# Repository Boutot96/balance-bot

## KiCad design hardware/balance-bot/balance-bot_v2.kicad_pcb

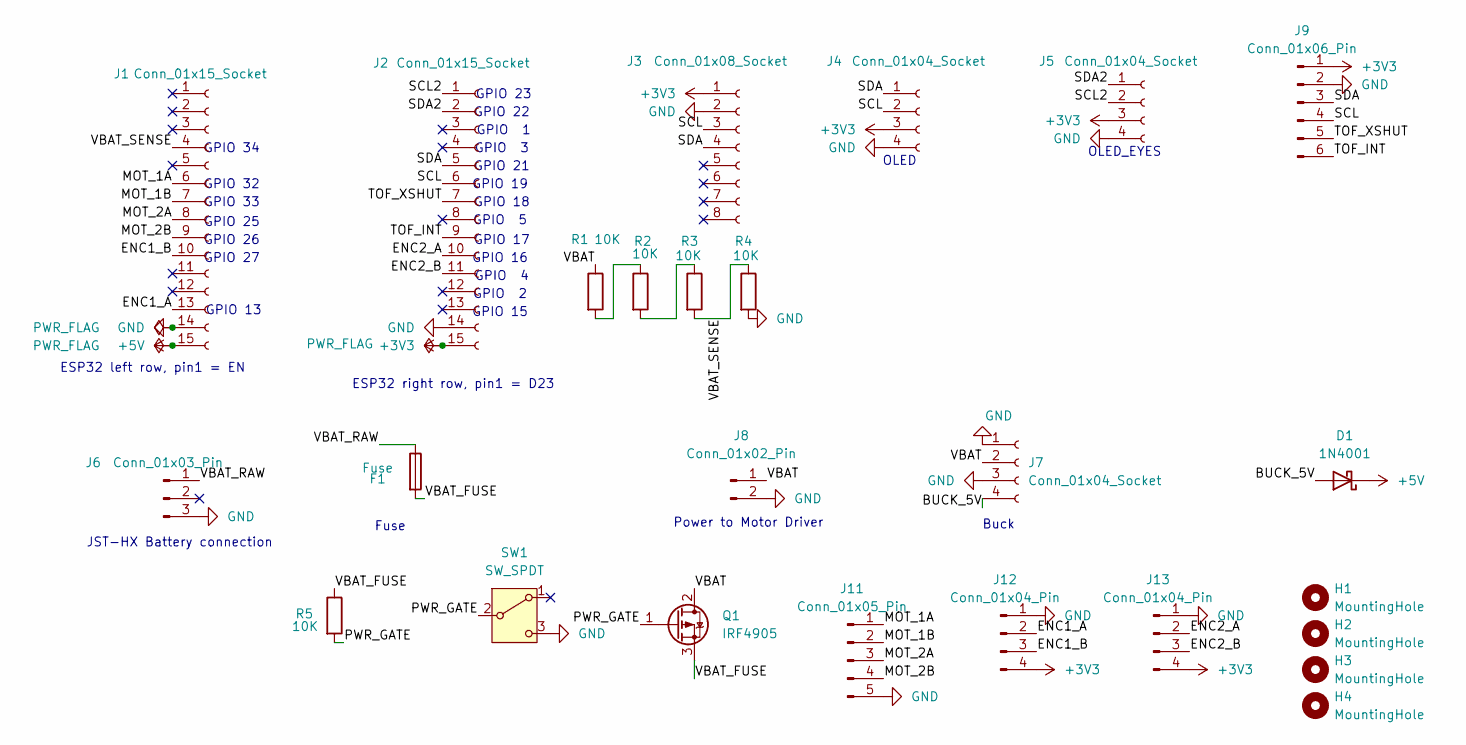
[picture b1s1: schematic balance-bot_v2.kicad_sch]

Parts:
D1: 1N4001; D_DO-41_SOD81_P10.16mm_Horizontal
F1: Fuse; Fuseholder_Cylinder-5x20mm_Schurter_0031_8201_Horizontal_Op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
H1, H2, H3, H4: MountingHole; MountingHole_3.2mm_M3
J1, J2: Conn_01x15_Socket; PinSocket_1x15_P2.54mm_Vertical
J3: Conn_01x08_Socket; PinSocket_1x08_P2.54mm_Vertical
J4, J5: Conn_01x04_Socket; PinSocket_1x04_P2.54mm_Vertical
J6: Conn_01x03_Pin; JST_XH_B3B-XH-A_1x03_P2.50mm_Vertical
J7: Conn_01x04_Socket; Buck_LM2596
J8: Conn_01x02_Pin; JST_XH_B2B-XH-A_1x02_P2.50mm_Vertical
J9: Conn_01x06_Pin; JST_XH_B6B-XH-A_1x06_P2.50mm_Vertical
J11: Conn_01x05_Pin; JST_XH_B5B-XH-A_1x05_P2.50mm_Vertical
J12, J13: Conn_01x04_Pin; JST_XH_B4B-XH-A_1x04_P2.50mm_Vertical
Q1: IRF4905; TO-220-3_Vertical
R1, R2, R3, R4, R5: 10K; R_Axial_DIN0207_L6.3mm_D2.5mm_P10.16mm_Horizontal
SW1: SW_SPDT; PinHeader_1x03_P2.54mm_Vertical

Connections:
+3V3: J2.15, J3.1, J4.3, J5.3, J9.1, J12.4, J13.4
+5V: D1.1 (K), J1.15
/BUCK_5V: D1.2 (A), J7.4
/ENC1_A: J1.13, J12.2
/ENC1_B: J1.10, J12.3
/ENC2_A: J2.10, J13.2
/ENC2_B: J2.11, J13.3
/MOT_1A: J1.6, J11.1
/MOT_1B: J1.7, J11.2
/MOT_2A: J1.8, J11.3
/MOT_2B: J1.9, J11.4
/PWR_GATE: Q1.1 (G), R5.2, SW1.2 (B)
/SCL: J2.6, J3.3, J4.2, J9.4
/SCL2: J2.1, J5.2
/SDA: J2.5, J3.4, J4.1, J9.3
/SDA2: J2.2, J5.1
/TOF_INT: J2.9, J9.6
/TOF_XSHUT: J2.7, J9.5
/VBAT: J7.2, J8.1, Q1.2 (D), R1.1
/VBAT_FUSE: F1.2, Q1.3 (S), R5.1
/VBAT_RAW: F1.1, J6.1
/VBAT_SENSE: J1.4, R3.2, R4.1
GND: J1.14, J2.14, J3.2, J4.4, J5.4, J6.3, J7.1, J7.3, J8.2, J9.2, J11.5, J12.1, J13.1, R4.2, SW1.3 (C)
unnamed: R1.2, R2.1
unnamed: R2.2, R3.1

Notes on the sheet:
GPIO 17
GPIO 15
GPIO 5
GPIO 2
GPIO 3
GPIO 26
GPIO 27
GPIO 34
Buck
Power to Motor Driver
GPIO 18
JST-HX Battery connection
ESP32 right row, pin1 = D23
OLED_EYES
GPIO 1
GPIO 16
GPIO 13
GPIO 32
GPIO 22
GPIO 4
GPIO 19
Fuse
GPIO 21
GPIO 33
GPIO 25
ESP32 left row, pin1 = EN
GPIO 23
OLED

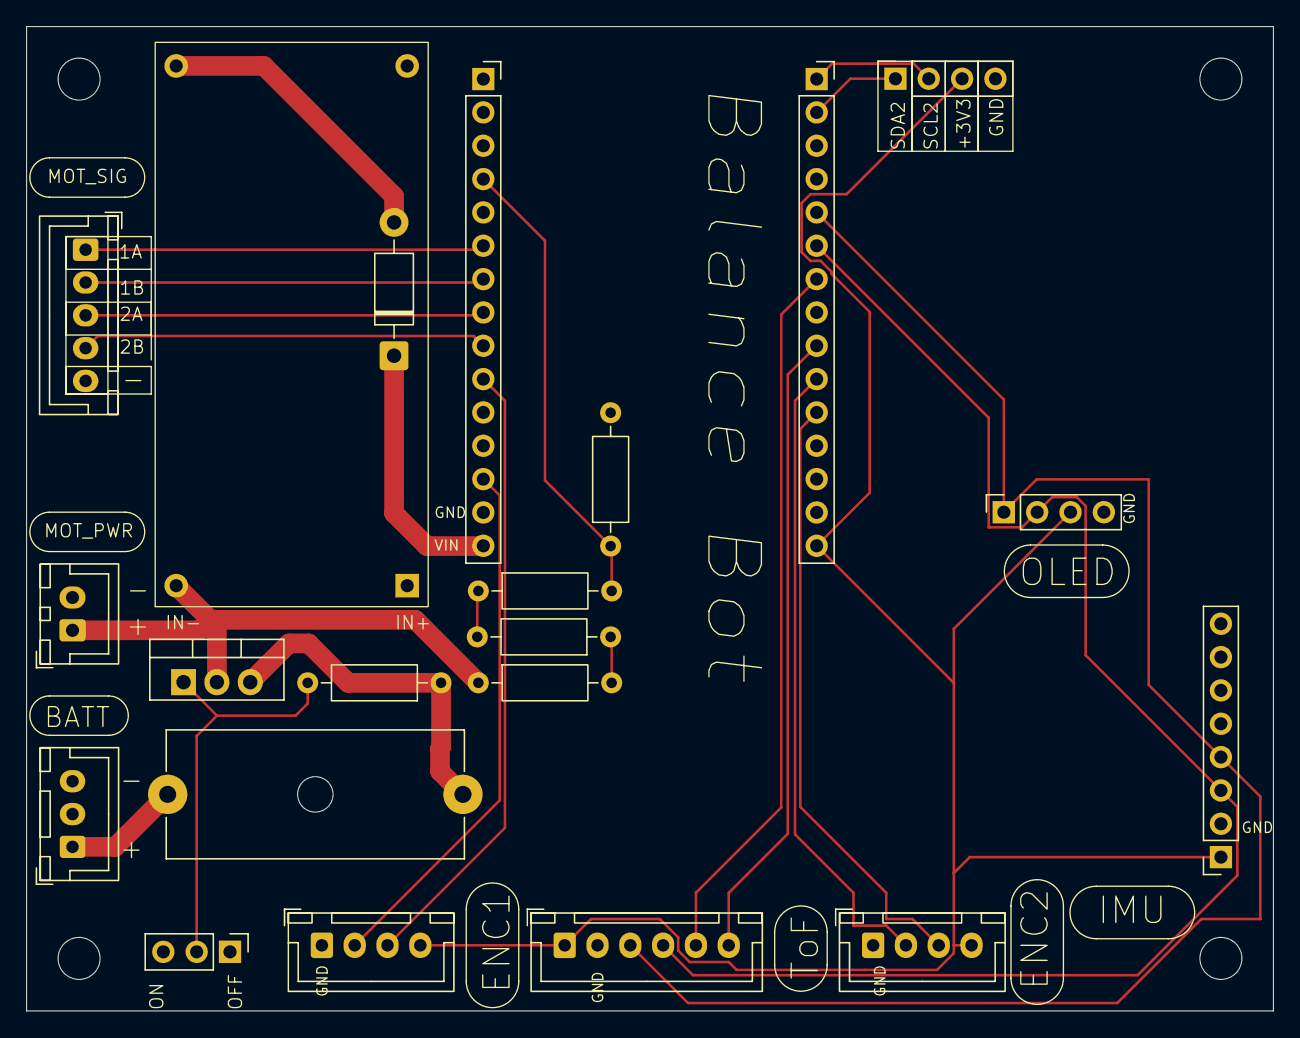
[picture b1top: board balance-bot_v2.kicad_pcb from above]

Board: 2 copper layers, 95.0 x 75.0 mm, 25 parts (0 on the bottom side), 25 nets.

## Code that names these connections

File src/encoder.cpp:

#include "encoder.h"
#include "config.h"
#include "timing.h"

static Every encTimer(ENC_PERIOD_MS);

static volatile int32_t counts[2]       = {0,0};
static int32_t          lastCounts[2]   = {0, 0};   // counts at the last speed update
static float            speeds[2]       = {0.0f,0.0f};
static uint32_t lastRun = 0;

static portMUX_TYPE encMux = portMUX_INITIALIZER_UNLOCKED;

static void IRAM_ATTR encLeftISR(){
    if(digitalRead(ENC1_A) == digitalRead(ENC1_B))  counts[ENC_LEFT]--;
    else                                            counts[ENC_LEFT]++;
}

static void IRAM_ATTR encRightISR(){
    if(digitalRead(ENC2_A) == digitalRead(ENC2_B))  counts[ENC_RIGHT]--;
    else                                            counts[ENC_RIGHT]++;
}

void encSetup(){
    pinMode(ENC1_A, INPUT_PULLUP);
    pinMode(ENC1_B, INPUT_PULLUP);
    pinMode(ENC2_A, INPUT_PULLUP);
    pinMode(ENC2_B, INPUT_PULLUP);

    attachInterrupt(digitalPinToInterrupt(ENC1_A), encLeftISR, CHANGE);
    attachInterrupt(digitalPinToInterrupt(ENC2_A), encRightISR, CHANGE);
    lastRun = micros();
}

void encUpdate(){
    uint32_t nowUs = micros();
    float dt = (nowUs - lastRun) / 1e6f;   // real seconds since last update
    if (dt <= 0.0f) return;
    lastRun = nowUs;
    const int   dirs[2] = { ENC1_DIR, ENC2_DIR };

        for (int side = 0; side < 2; side++) {

            int32_t now   = encCount(side);
            int32_t delta = now - lastCounts[side];      // how far it moved
            lastCounts[side] = now;                      // remember for next time

            float rps = (delta / dt) / ENC_COUNTS_PER_REV;   // revolutions per second
            rps *= dirs[side];                                 // forward = positive

            speeds[side] = 0.7f * speeds[side] + 0.3f * rps;   // smooth
        }
}

void encService() {
    if (encTimer.ready()) encUpdate();
}

int32_t encCount(int side)  { 
    int32_t copy = 0;
    portENTER_CRITICAL(&encMux);
    copy = counts[side];
    portEXIT_CRITICAL(&encMux);
    return copy;
}

float encSpeed(int side)    { return speeds[side]; }
